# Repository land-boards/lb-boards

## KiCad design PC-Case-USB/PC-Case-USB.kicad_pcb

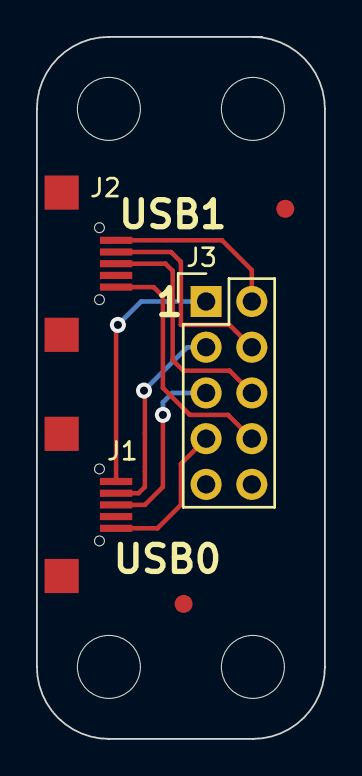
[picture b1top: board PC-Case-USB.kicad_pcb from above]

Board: 2 copper layers, 16.0 x 39.0 mm, 10 parts (1 on the bottom side), 8 nets.

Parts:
FID1, FID2: CONN_1; FIDUCIAL
J1, J2: USB-MICRO-B; USB_Micro-B-Wellco-SMT
J3: CONN_01X10; Pin_Header_Straight_2x05
MTG1, MTG2, MTG3, MTG4: CONN_1; MountingHole_3.5mm
TEST: COUPON; REV_BLOCK

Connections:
unnamed: J1.1, J3.1
unnamed: J1.2, J3.3
unnamed: J1.3, J3.5
unnamed: J1.5, J3.7
unnamed: J2.1, J3.2
unnamed: J2.2, J3.4
unnamed: J2.3, J3.6
unnamed: J2.5, J3.8

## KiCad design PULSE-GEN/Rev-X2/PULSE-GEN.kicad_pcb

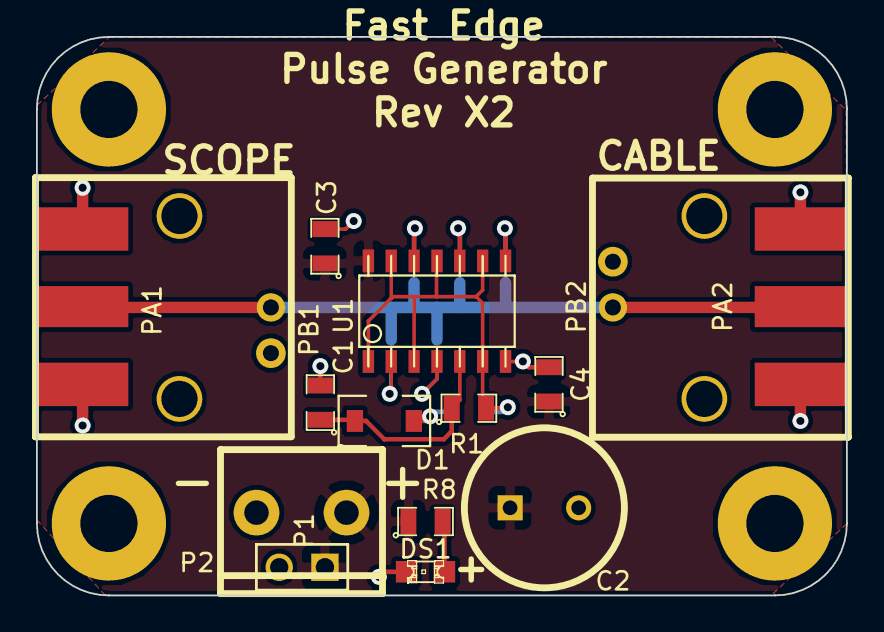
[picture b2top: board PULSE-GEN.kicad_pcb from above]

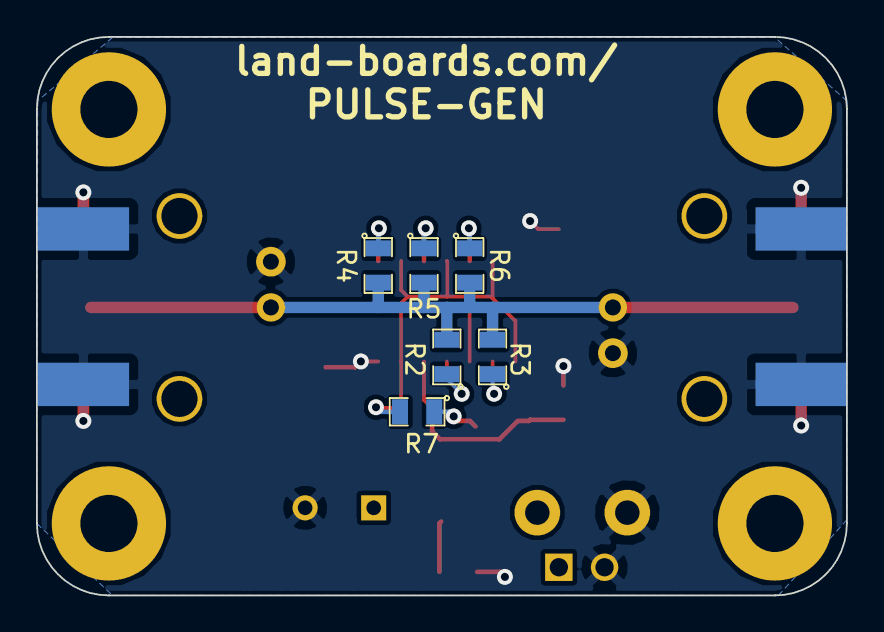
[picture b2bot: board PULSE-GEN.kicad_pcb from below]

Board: 2 copper layers, 45.0 x 31.0 mm, 25 parts (6 on the bottom side), 12 nets.

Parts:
C1: 47nF; SM0805
C2: 100uF; C1.5V8V
C3, C4: 0.1uF; SM0805
D1: 1N4148; SOD-123
DS1: LED; LED-0805
MTG1, MTG2, MTG3, MTG4: CONN_1; MTG-4-40
P1: CONN_2; PIN_ARRAY_2X1
P2: CONN_2; TB2-5MM
PA1, PA2: SMA; SMA_EDGE
PB1, PB2: BNC; BNC-RT
R1: 33K; SM0805
R2, R3, R4, R5, R6, R8: 240; SM0805
R7: 150; SM0805
U1: 74AC14; so-14

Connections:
GND: C1.2, C2.2, C3.2, C4.2, DS1.2, P1.2, P2.2, PA1.2, PA2.2, PB1.2, PB2.2, U1.7
unnamed: DS1.1, R8.2
unnamed: D1.2, R7.1
unnamed: C1.1, D1.1, R1.1, U1.5
unnamed: R2.1, U1.4
unnamed: R3.1, U1.2
unnamed: R1.2, R7.2, U1.1, U1.3, U1.6, U1.9, U1.11, U1.13
unnamed: PA1.1, PA2.1, PB1.1, PB2.1, R2.2, R3.2, R4.2, R5.2, R6.2
unnamed: R4.1, U1.8
unnamed: R5.1, U1.10
unnamed: R6.1, U1.12
VCC: C2.1, C3.1, C4.1, P1.1, P2.1, R8.1, U1.14

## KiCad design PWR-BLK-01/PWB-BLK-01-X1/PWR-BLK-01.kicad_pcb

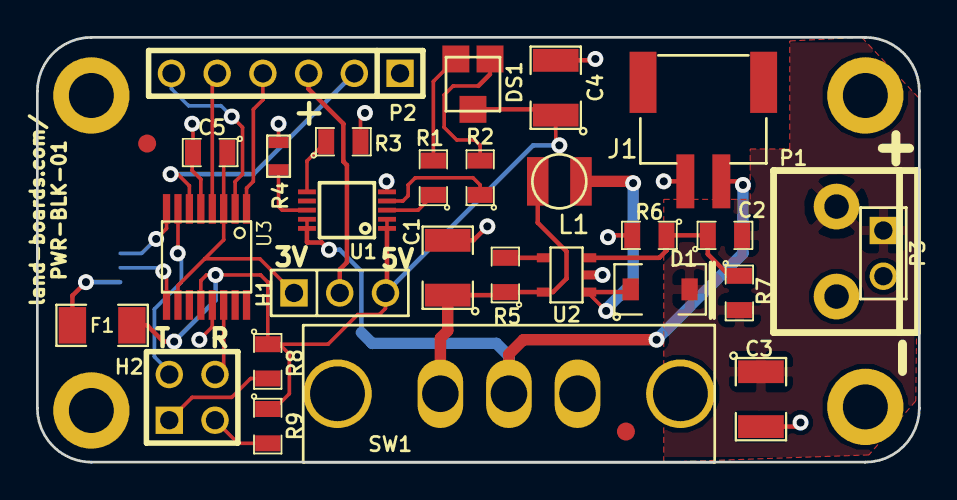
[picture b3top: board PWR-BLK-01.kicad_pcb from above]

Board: 2 copper layers, 49.0 x 23.6 mm, 35 parts (1 on the bottom side), 27 nets.

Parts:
C1, C3: 4.7uF; SM1210
C2: 680pF; SM0805
C4: 10uF; SM1210
C5: 0.1uF; SM0805
D1: MBR0520LT1G; SOD-123
DS1: LED2C_CA; SOT23_LED2C
F1: FUSE; SM1206
FID1, FID2: CONN_1; FIDUCIAL
H1: CONN_3; PIN_ARRAY_3X1
H2: CONN_2X2; PIN_ARRAY_2X2
J1: JST_2; JST-2-SMT
J2: USB-B; USB-B-MINI
L1: 10uH; IND-3MM
MTG1, MTG2, MTG3, MTG4: CONN_1; MTG-2.5MM
P1: CONN_2; TB2-5MM
P2: CONN_6; PIN_ARRAY-6X1
P3: CONN_2; PIN_ARRAY_2X1
R1, R2: 470; SM0805
R3: 2.2K; SM0805
R4: NTC-10K; SM0603
R5: 1M; SM0805
R6: 1K; SM0805
R7: 3.09K; SM0805
R8, R9: 270; SM0805
SW1: SW-SPDT; SW-SPDT-SLIDE
U1: MCP73833; MSOP10-0.5
U2: LMR62014; SOT23-5
U3: FT230XS; ssop-16

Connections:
/5V Power Supply/3.7V: C1.1, L1.1, R5.1, SW1.1, U2.5
/5V Power Supply/+5VOUT: C2.2, C3.1, D1.2, P1.1, P3.1, R7.2
/FTDI/+3.3V: C5.1, H1.1, U3.3, U3.10
/FTDI/CTS: P2.2, U3.6
/FTDI/DM: J2.2, U3.9
/FTDI/DP: J2.3, U3.8
/FTDI/PUP0: H2.1, R8.2
/FTDI/PUP1: H2.3, R9.2
/FTDI/RTS: P2.6, U3.2
/FTDI/RX: P2.5, U3.4
/FTDI/RXLED*: H2.4, U3.14
/FTDI/TX: P2.4, U3.1
/FTDI/TXLED*: H2.2, U3.7
/FTDI/VCC: H1.2, P2.3
/FTDI/VUSB: C4.1, DS1.ANOD, F1.2, H1.3, R8.1, R9.1, U1.1, U1.2, U3.12
/LiPo Battery Charger/VB-3.7: J1.2, SW1.2, U1.9, U1.10
GND: C1.2, C3.2, C4.2, C5.2, J1.1, J2.4, P1.2, P2.1, P3.2, R3.2, R4.2, R6.2, U1.5, U2.2, U3.5, U3.13
unnamed: R3.1, U1.6
unnamed: R4.1, U1.8
unnamed: DS1.RED, R1.2
unnamed: DS1.GRN, R2.2
unnamed: R1.1, U1.3
unnamed: R2.1, U1.4
unnamed: C2.1, R6.1, R7.1, U2.3
unnamed: R5.2, U2.4
unnamed: D1.1, L1.2, U2.1
unnamed: F1.1, J2.1

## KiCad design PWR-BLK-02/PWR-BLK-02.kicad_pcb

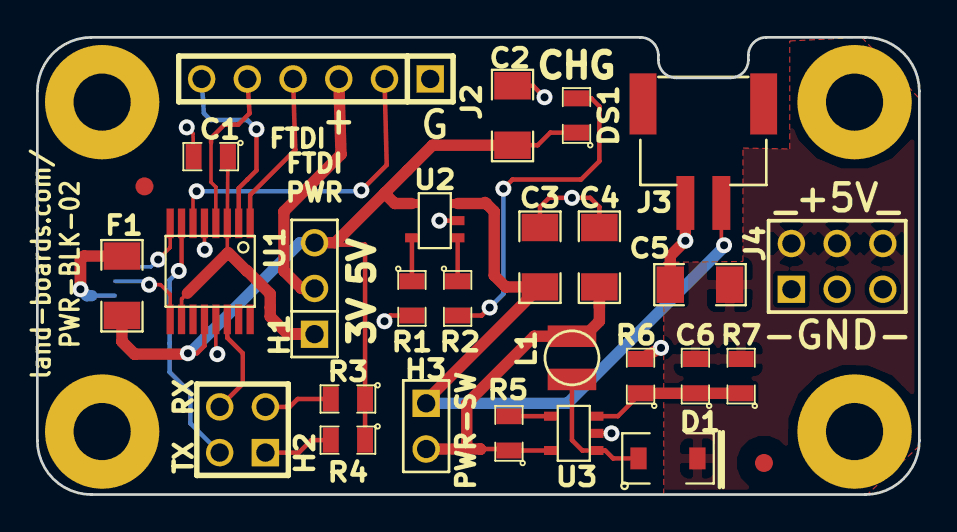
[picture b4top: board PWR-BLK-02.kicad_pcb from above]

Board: 2 copper layers, 49.0 x 25.4 mm, 33 parts (1 on the bottom side), 24 nets.

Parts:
C1: 0.1uF; SM0805
C2, C3: 10uF; SM1206
C4, C5: 4.7uF; SM1206
C6: 680pF; SM0805
D1: MBR0520LT1G; SOD-123
DS1: LED; SM0805
F1: FUSE; SM1206
FID1, FID2: CONN_1; FIDUCIAL
H1: CONN_3; PIN_ARRAY_3X1
H2: CONN_2X2; PIN_ARRAY_2X2
H3: CONN_2; PIN_ARRAY_2X1
J1: USB-B; USB-B-MINI
J2: CONN_6; PIN_ARRAY-6X1
J3: JST_2; JST-2-SMT
J4: CONN_3X2; PIN_ARRAY_3X2
L1: 10uH; IND-3MM
MTG1, MTG2, MTG3, MTG4: CONN_1; MTG-4-40
R1: 2.2K; SM0805
R2: 470; SM0805
R3, R4: 270; SM0805
R5: 1M; SM0805
R6: 1K; SM0805
R7: 3.09K; SM0805
U1: FT230XS; ssop-16
U2: MCP73831; SOT23-5
U3: LMR62014; SOT23-5

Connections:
/5V Power Supply/3.7V: C4.1, H3.2, L1.1, R5.1, U3.5
/5V Power Supply/+5VOUT: C5.1, C6.2, D1.2, J4.2, J4.4, J4.6, R7.2
/FTDI/+3.3V: C1.1, H1.1, U1.3, U1.10
/FTDI/CTS: J2.2, U1.6
/FTDI/DM: J1.2, U1.9
/FTDI/DP: J1.3, U1.8
/FTDI/PUP0: H2.1, R4.2
/FTDI/PUP1: H2.3, R3.2
/FTDI/RTS: J2.6, U1.2
/FTDI/RX: J2.5, U1.4
/FTDI/RXLED*: H2.4, U1.14
/FTDI/TX: J2.4, U1.1
/FTDI/TXLED*: H2.2, U1.7
/FTDI/VCC: H1.2, J2.3
/FTDI/VUSB: C2.1, DS1.1, F1.2, H1.3, R3.1, R4.1, U1.12, U2.4
/LiPo Battery Charger/VB-3.7: C3.1, H3.1, J3.2, U2.3
GND: C1.2, C2.2, C3.2, C4.2, C5.2, J1.4, J2.1, J3.1, J4.1, J4.3, J4.5, R1.2, R6.2, U1.5, U1.13, U2.2, U3.2
unnamed: R2.1, U2.1
unnamed: DS1.2, R2.2
unnamed: R1.1, U2.5
unnamed: C6.1, R6.1, R7.1, U3.3
unnamed: R5.2, U3.4
unnamed: D1.1, L1.2, U3.1
unnamed: F1.1, J1.1

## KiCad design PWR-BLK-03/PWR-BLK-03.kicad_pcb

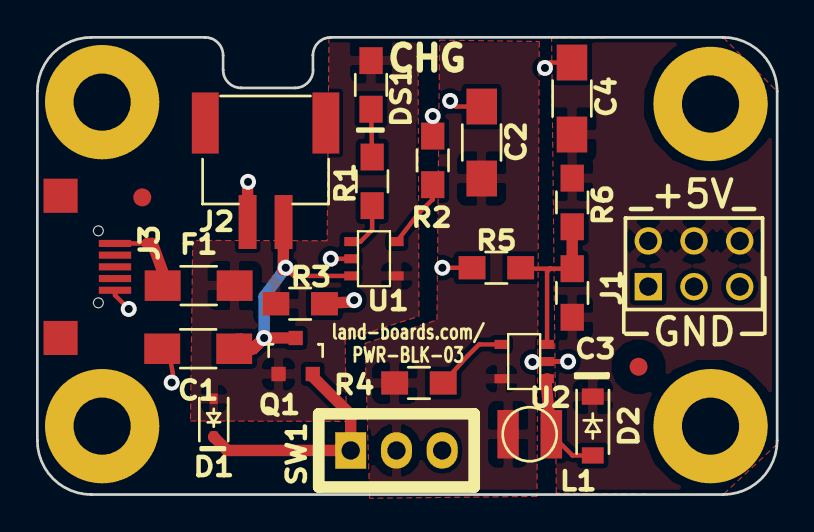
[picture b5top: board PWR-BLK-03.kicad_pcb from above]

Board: 2 copper layers, 41.1 x 25.4 mm, 28 parts (0 on the bottom side), 13 nets.

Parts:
C1: 10uF; R_1206_HandSoldering
C2, C4: 4.7uF; R_1206_HandSoldering
C3: 680pF; R_0805_HandSoldering
D1: D_Schottky_FixedPinout; SOD-323
D2: MBR0520LT1G; SOD-123-FIXED
DS1: LED; R_0805_HandSoldering
F1: FUSE; R_1206_HandSoldering
FID1, FID2: CONN_1; FIDUCIAL
J1: CONN_3X2; PIN_ARRAY_3X2
J2: JST_2; JST-2-SMT
J3: USB-MICRO-B; USB_Micro-B-Wellco-SMT
L1: 10uH; IND-3MM
MTG1, MTG2, MTG3, MTG4: CONN_1; MTG-4-40
Q1: PMV48XP; SOT-23
R1: 470; R_0805_HandSoldering
R2: 2.2K; R_0805_HandSoldering
R3: 10K; R_0805_HandSoldering
R4: 1M; R_0805_HandSoldering
R5: 1K; R_0805_HandSoldering
R6: 3.09K; R_0805_HandSoldering
SW1: Switch_SPDT_x2; SPDT0.1IN
U1: MCP73831; SOT23-5
U2: LMR62014; SOT23-5

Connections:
/5V Power Supply/3.7V: C2.1, L1.1, R4.1, SW1.2, U2.5
/5V Power Supply/+5VOUT: C3.2, C4.1, D2.2, J1.2, J1.4, J1.6, R6.2
/5V Power Supply/VFB: D2.1, L1.2, U2.1
/LiPo Battery Charger/VB-3.7: D1.1, Q1.2, SW1.1
/USB/+5VUSB: D1.2, DS1.1, F1.2, Q1.1, R3.1, U1.4
GND: C1.2, C2.2, C4.2, J1.1, J1.3, J1.5, J2.1, J3.5, R2.2, R3.2, R5.2, U1.2, U2.2
unnamed: C1.1, J2.2, Q1.3, U1.3
unnamed: C3.1, R5.1, R6.1, U2.3
unnamed: DS1.2, R1.2
unnamed: F1.1, J3.1
unnamed: R1.1, U1.1
unnamed: R2.1, U1.5
unnamed: R4.2, U2.4
